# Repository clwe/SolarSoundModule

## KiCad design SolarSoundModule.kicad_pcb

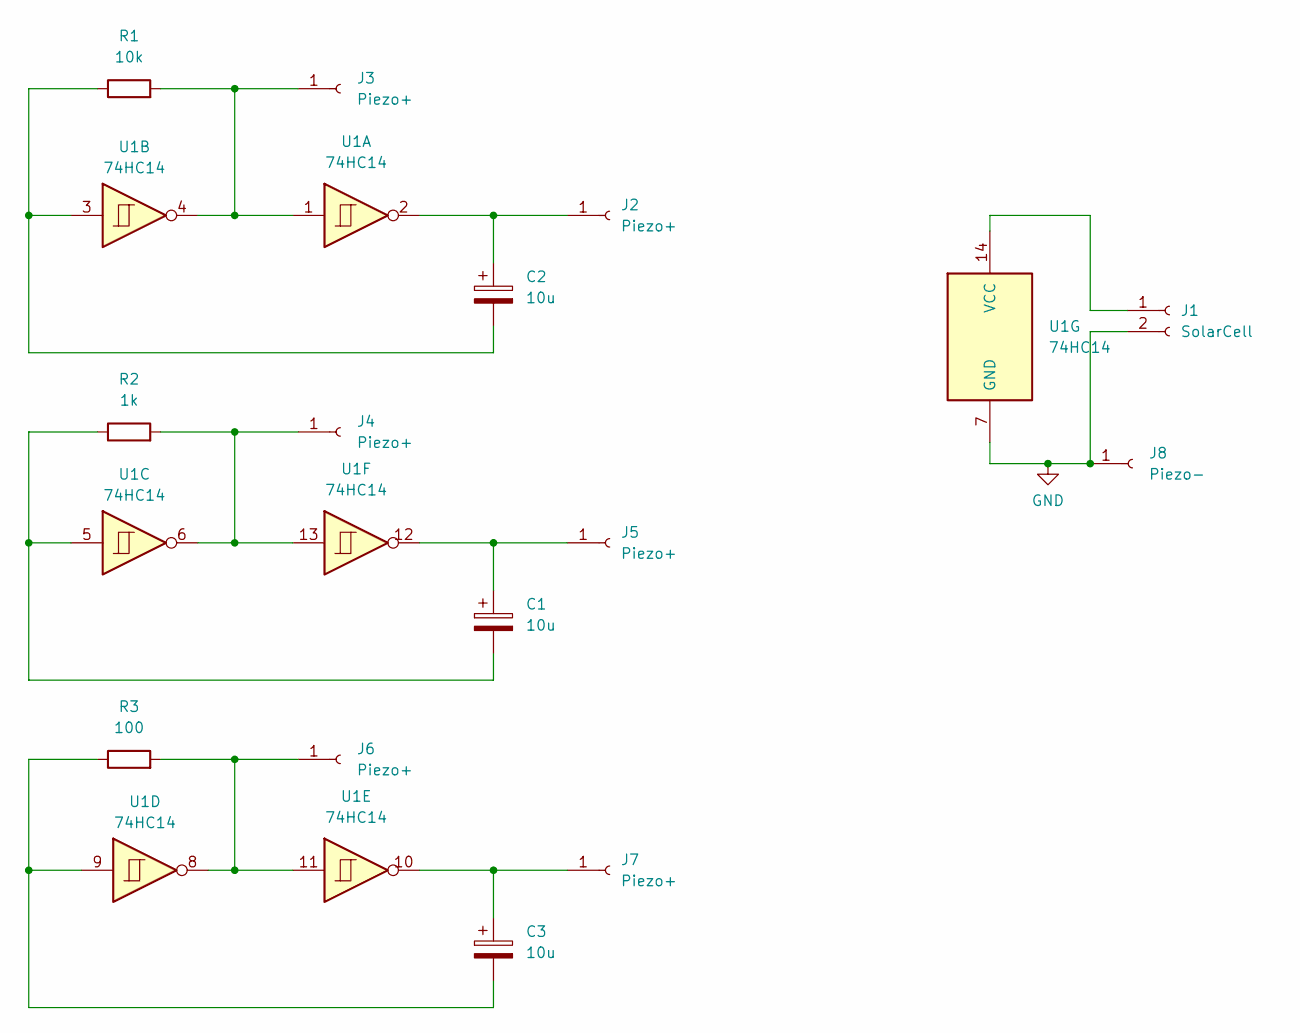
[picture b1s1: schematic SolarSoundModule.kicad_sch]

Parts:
C1, C2, C3: 10u; CP_Radial_D5.0mm_P2.50mm
J1: SolarCell; PinHeader_1x02_P2.54mm_Vertical
J2, J3, J4, J5, J6, J7: Piezo+; PinHeader_1x01_P2.54mm_Vertical
J8: Piezo-; PinHeader_1x01_P2.54mm_Vertical
R1: 10k; R_Axial_DIN0207_L6.3mm_D2.5mm_P10.16mm_Horizontal
R2: 1k; R_Axial_DIN0207_L6.3mm_D2.5mm_P10.16mm_Horizontal
R3: 100; R_Axial_DIN0207_L6.3mm_D2.5mm_P10.16mm_Horizontal
U1: 74HC14; DIP-14_W7.62mm_LongPads

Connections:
GND: J1.2, J8.1, U1.7 (GND)
unnamed: C1.2, R2.1, U1.5
unnamed: C2.2, R1.1, U1.3
unnamed: C3.2, R3.1, U1.9
unnamed: J1.1, U1.14 (VCC)
unnamed: C2.1, J2.1, U1.2
unnamed: J3.1, R1.2, U1.1, U1.4
unnamed: J4.1, R2.2, U1.6, U1.13
unnamed: C1.1, J5.1, U1.12
unnamed: J6.1, R3.2, U1.8, U1.11
unnamed: C3.1, J7.1, U1.10

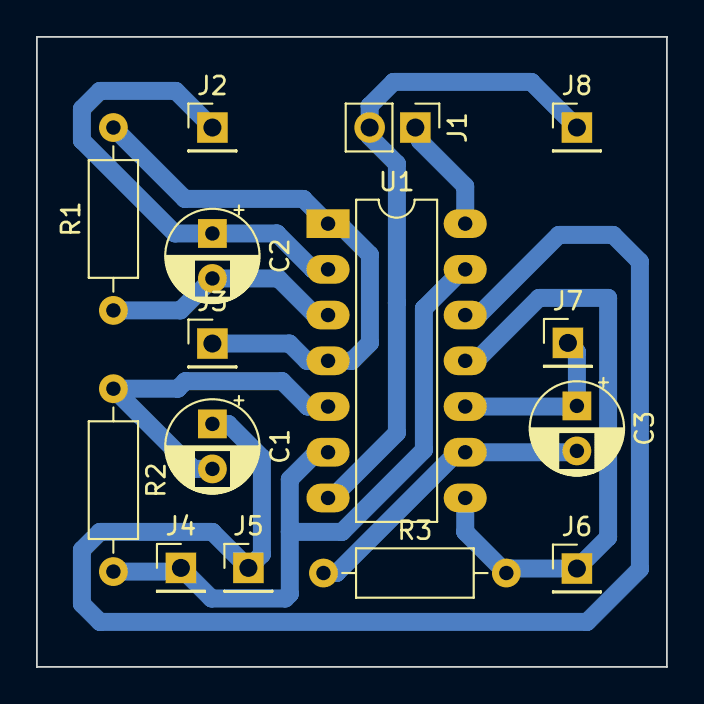
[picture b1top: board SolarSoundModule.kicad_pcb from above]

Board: 2 copper layers, 35.0 x 35.0 mm, 15 parts (0 on the bottom side), 11 nets.

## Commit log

2024-03-25 adds kicad project
2024-03-25 adds FlatcamFiles
